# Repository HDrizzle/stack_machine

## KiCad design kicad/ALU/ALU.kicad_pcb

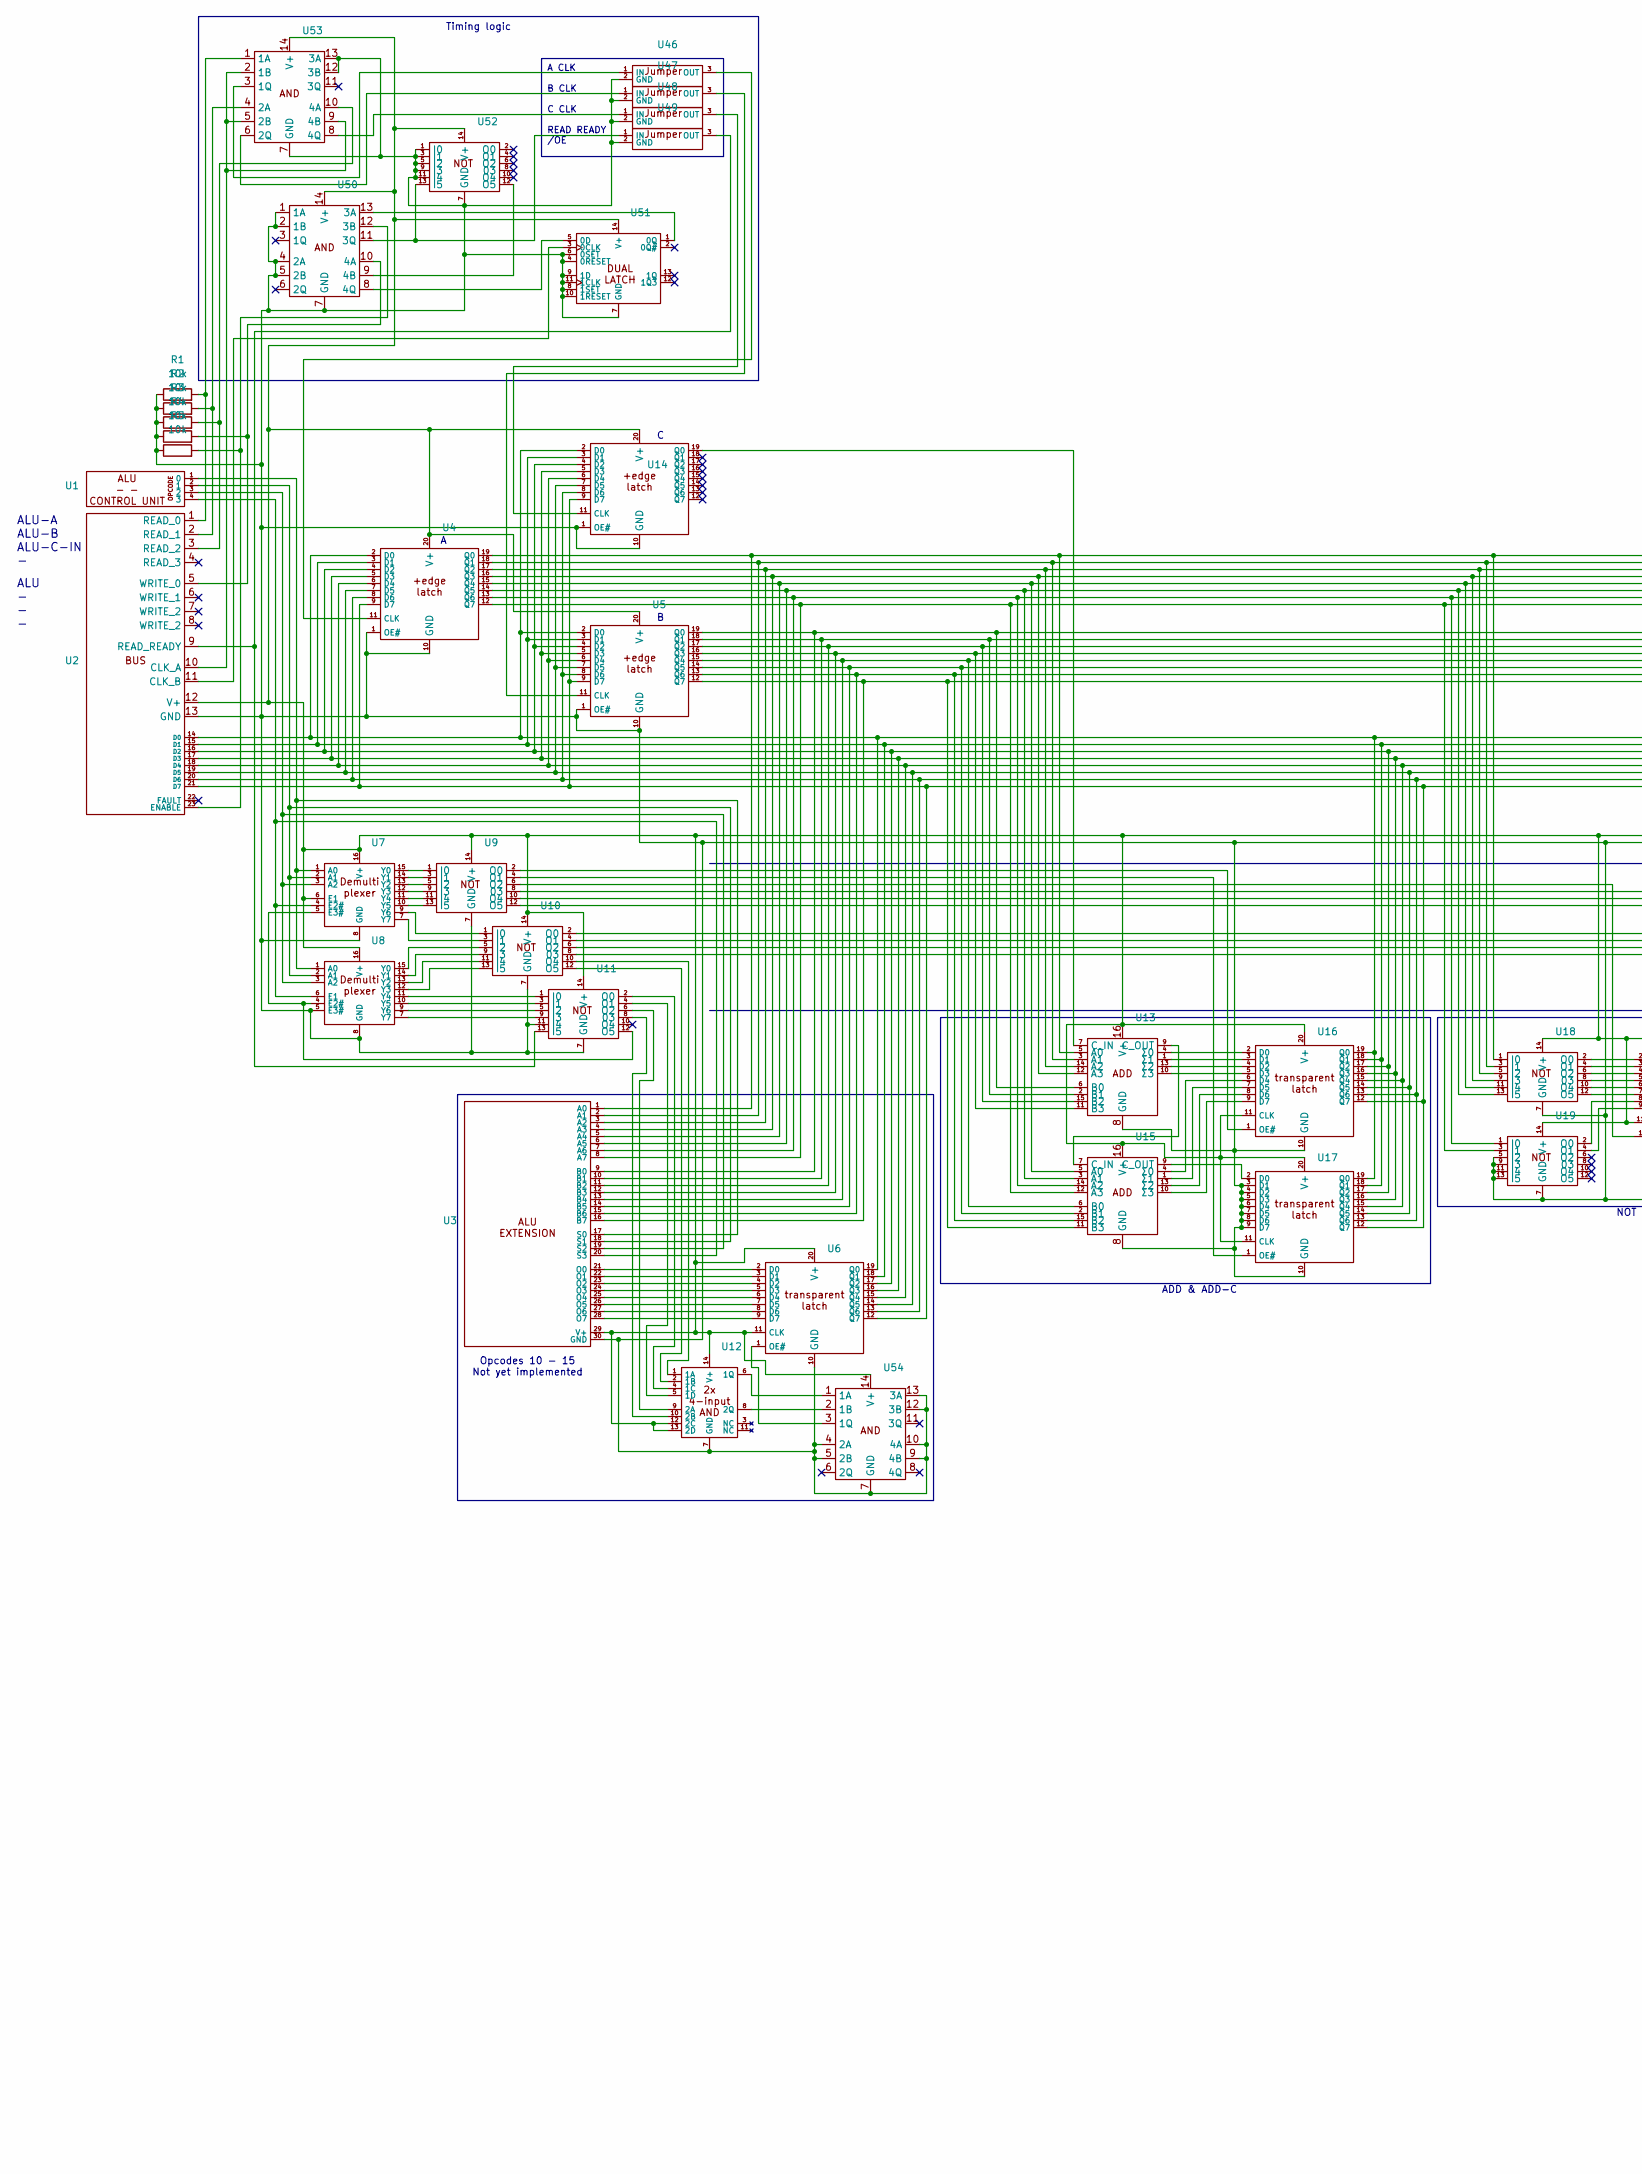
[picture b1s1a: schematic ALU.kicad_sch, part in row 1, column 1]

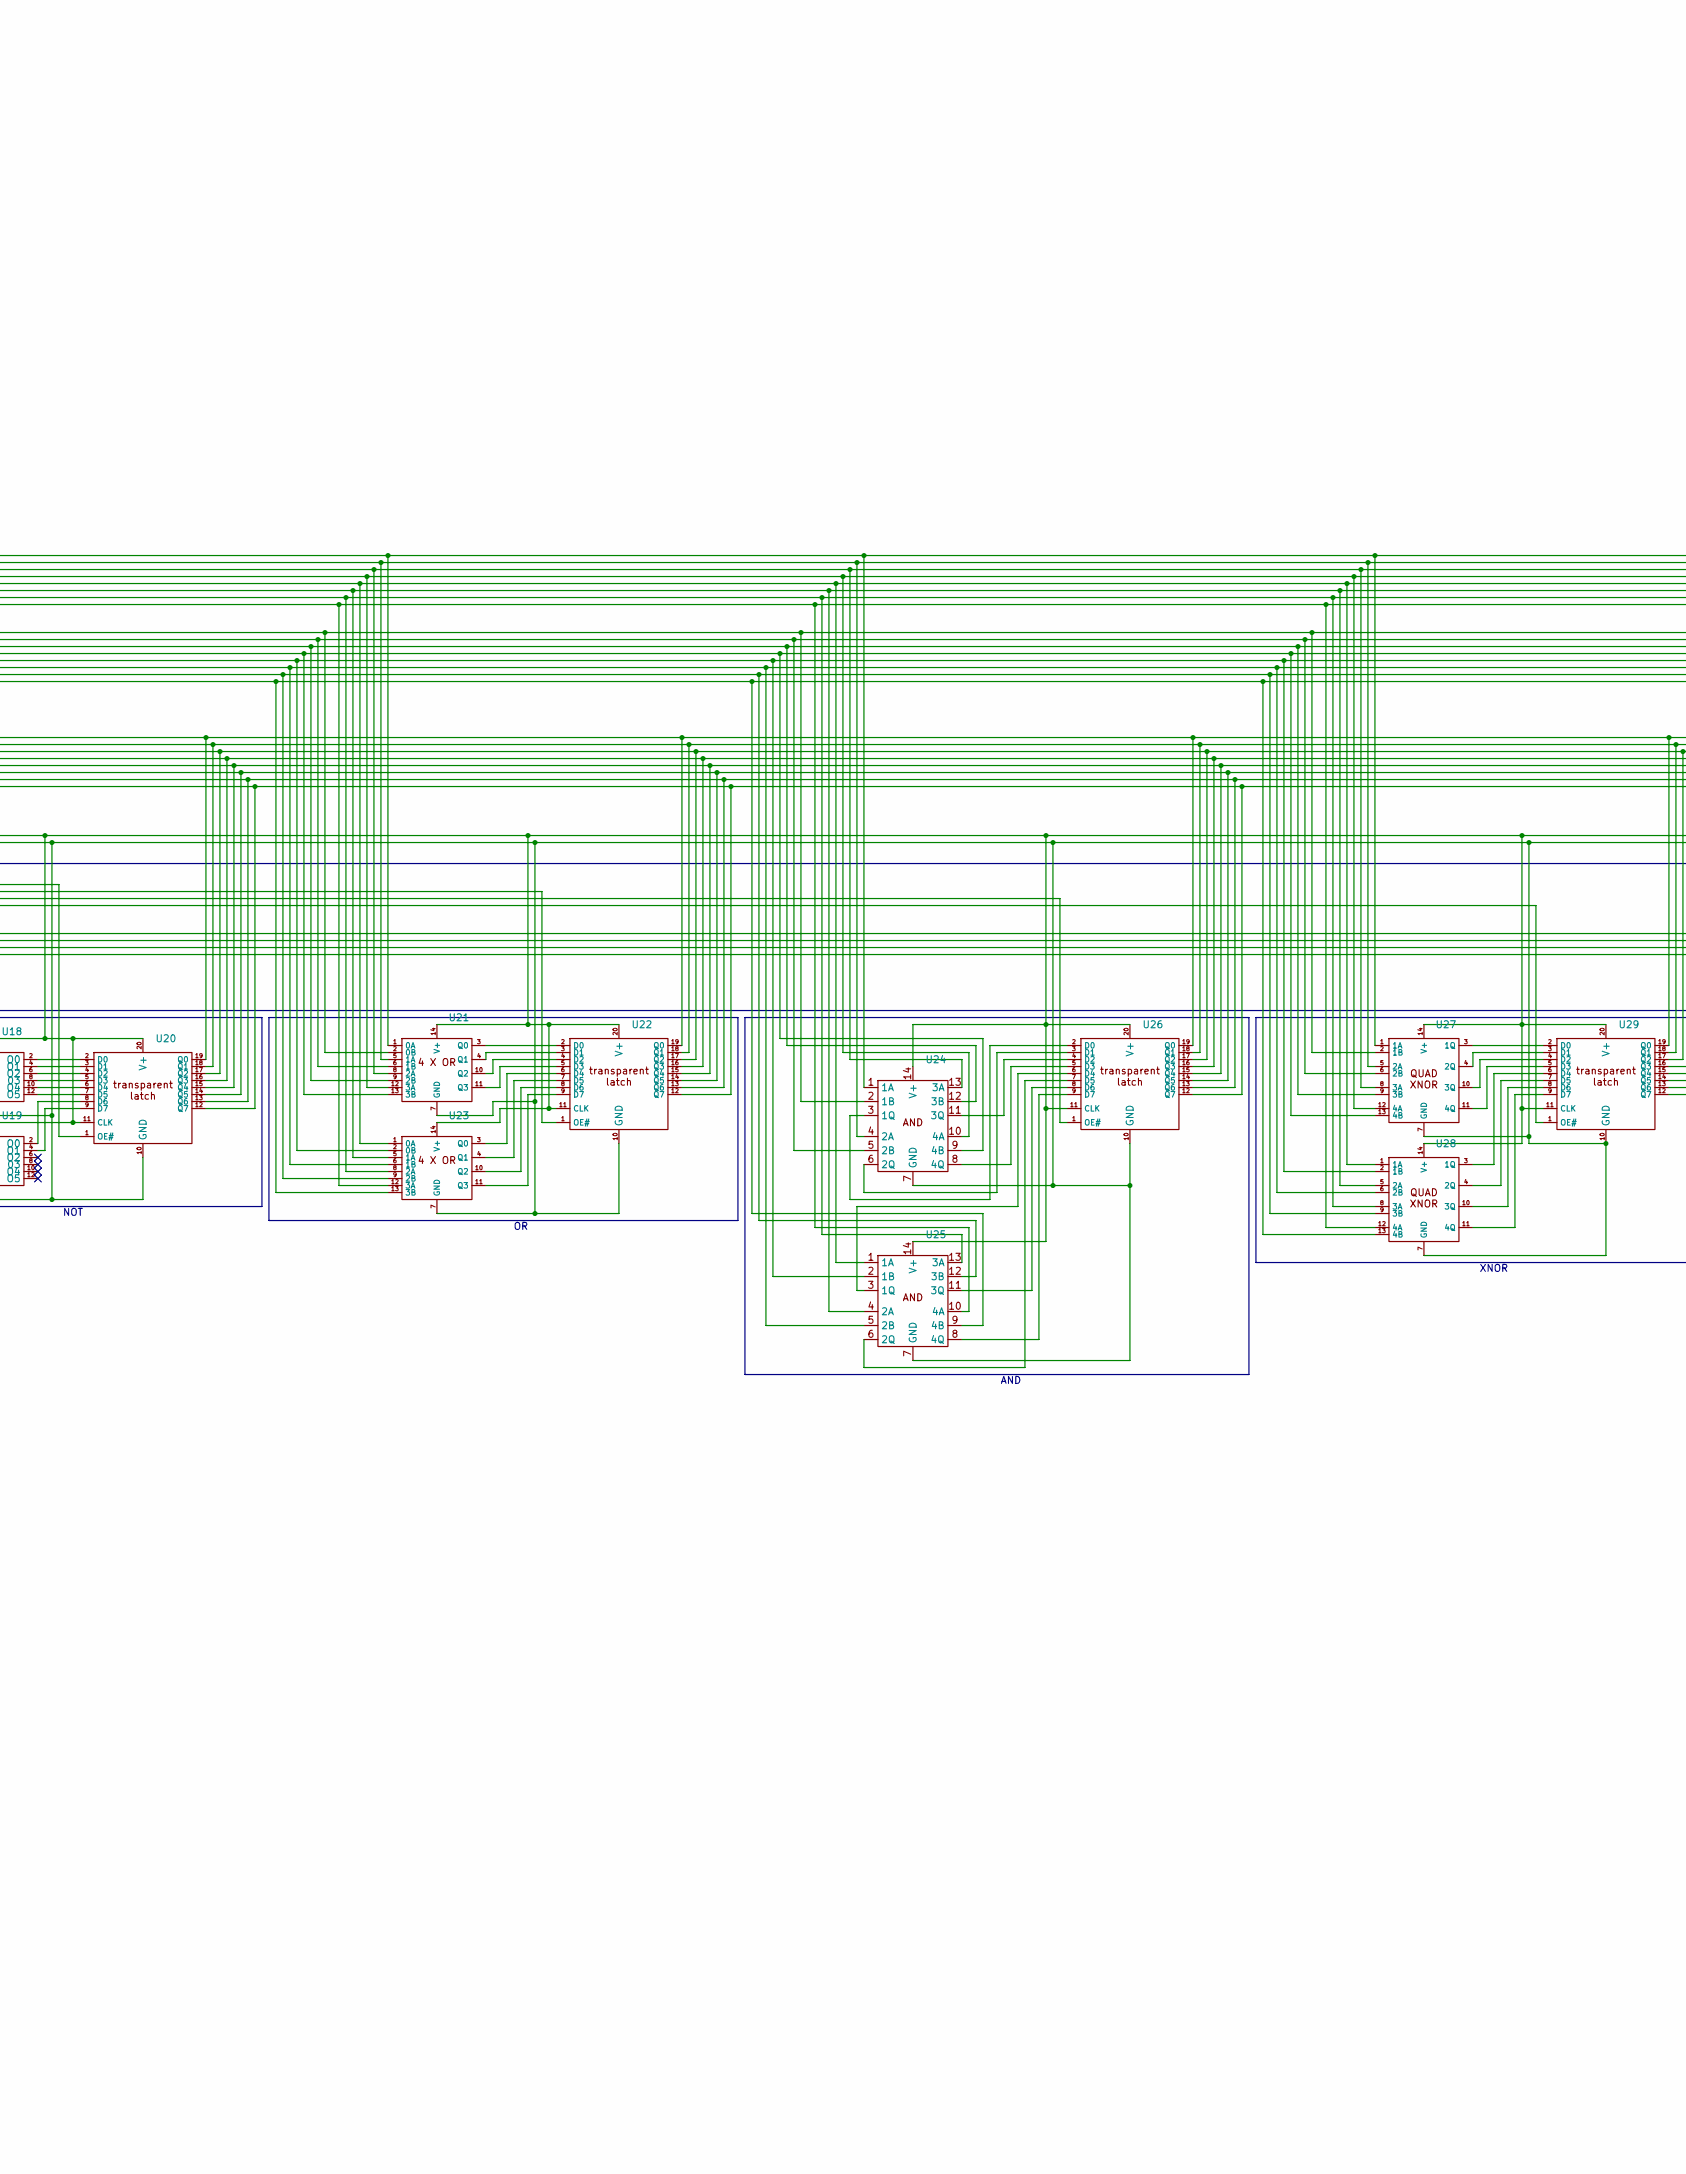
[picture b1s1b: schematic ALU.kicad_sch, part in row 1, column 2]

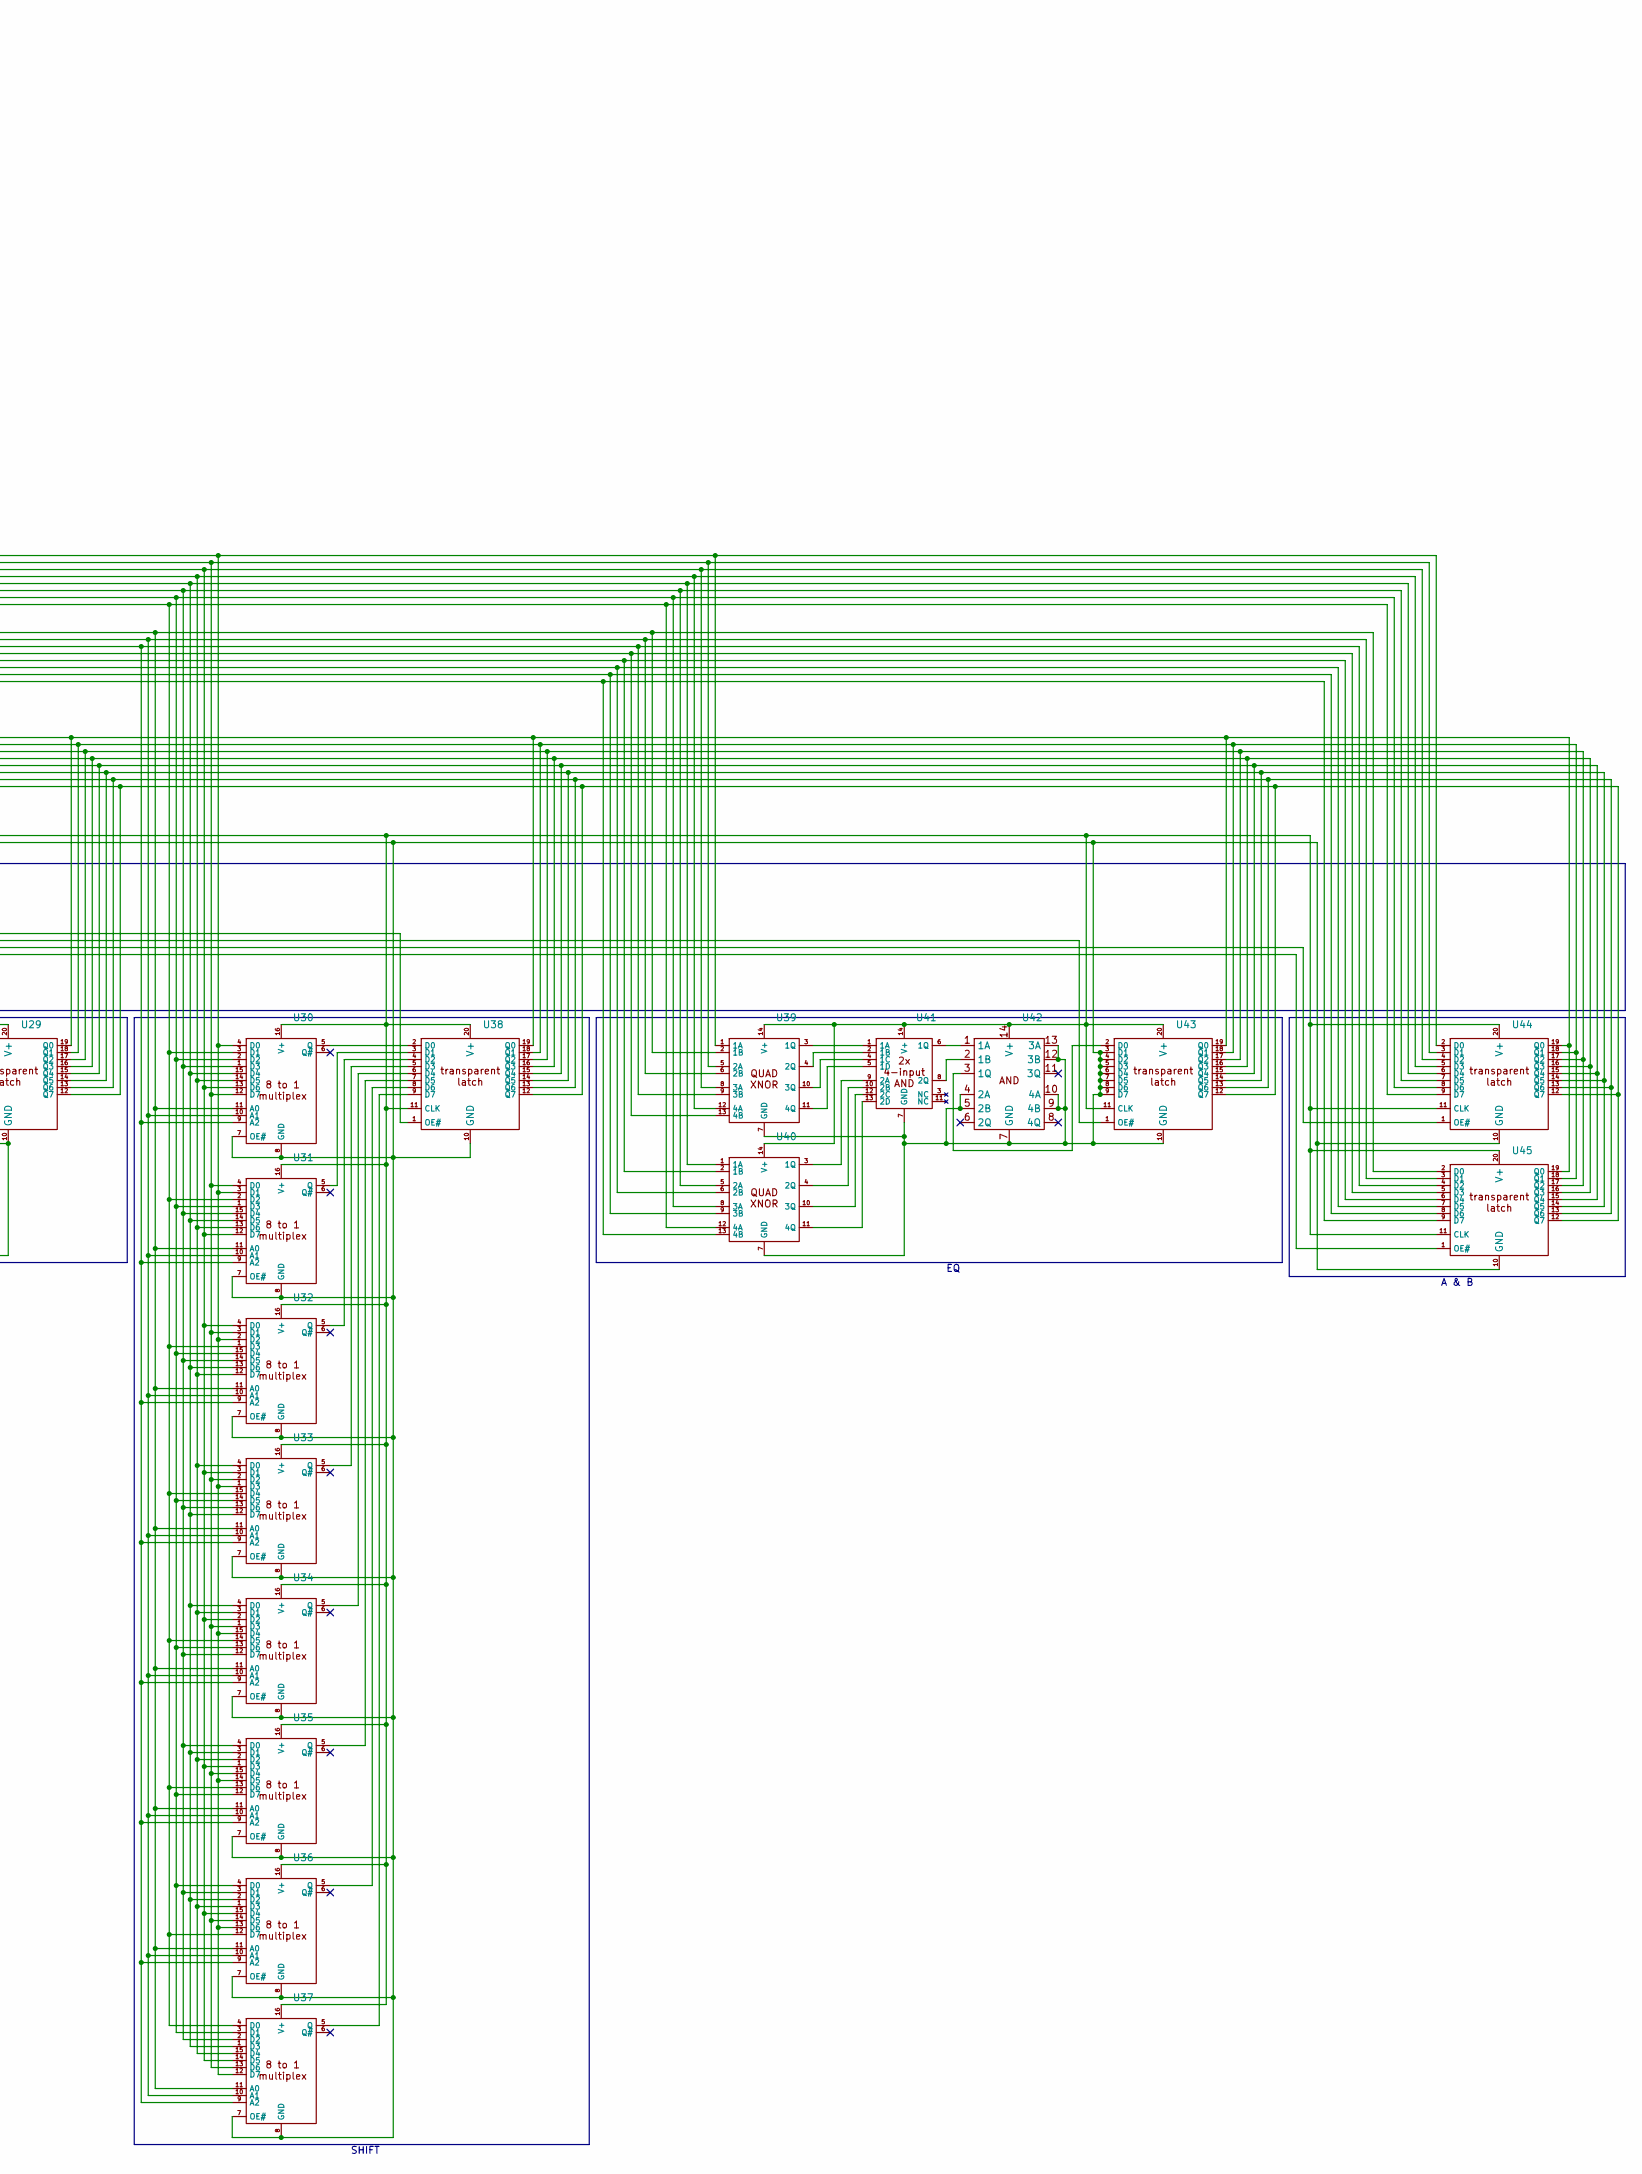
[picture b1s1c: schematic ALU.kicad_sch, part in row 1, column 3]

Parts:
R1, R2, R3, R4, R5: 10k; 0.4_pitch_resistor
U1: PinHeader_1x04_P2.54mm_Vertical
U2: PinHeader_1x23_P2.54mm_Vertical
U3: PinHeader_1x30_P2.54mm_Horizontal
U4, U5, U6, U14, U16, U17, U20, U22, U26, U29, U38, U43, U44, U45: DIP-20_W7.62mm
U7, U8, U13, U15, U30, U31, U32, U33, U34, U35, U36, U37: DIP-16_W7.62mm
U9, U10, U11, U12, U18, U19, U21, U23, U24, U25, U27, U28, U39, U40, U41, U42, U50, U51, U52, U53, U54: DIP-14_W7.62mm
U46, U47, U48, U49: jumper

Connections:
unnamed: U1.1 (0), U3.17 (S0), U7.1 (A0), U8.1 (A0)
unnamed: U1.2 (1), U3.18 (S1), U7.2 (A1), U8.2 (A1)
unnamed: U1.3 (2), U3.19 (S2), U7.3 (A2), U8.3 (A2)
unnamed: U1.4 (3), U3.20 (S3), U7.4 (E2#), U8.6 (E1)
unnamed: U2.10 (CLK_A), U53.2 (1B), U53.5 (2B), U53.9 (4B)
unnamed: U2.11 (CLK_B), U51.3 (0CLK)
unnamed: R5.2, U2.23 (ENABLE), U50.12 (3B)
unnamed: R1.2, U2.1 (READ_0), U53.1 (1A)
unnamed: R2.2, U2.2 (READ_1), U53.4 (2A)
unnamed: R3.2, U2.3 (READ_2), U53.10 (4A)
unnamed: R4.2, U2.5 (WRITE_0), U50.10 (4A)
unnamed: U3.21 (O0), U6.2 (D0)
unnamed: U3.22 (O1), U6.3 (D1)
unnamed: U3.23 (O2), U6.4 (D2)
unnamed: U3.24 (O3), U6.5 (D3)
unnamed: U3.25 (O4), U6.6 (D4)
unnamed: U3.26 (O5), U6.7 (D5)
unnamed: U3.27 (O6), U6.8 (D6)
unnamed: U3.28 (O7), U6.9 (D7)
unnamed: U4.11 (CLK), U46.3 (OUT)
unnamed: U7.15 (Y0), U9.1 (I0)
unnamed: U7.14 (Y1), U9.3 (I1)
unnamed: U7.13 (Y2), U9.5 (I2)
unnamed: U7.12 (Y3), U9.9 (I3)
unnamed: U7.11 (Y4), U9.11 (I4)
unnamed: U7.10 (Y5), U9.13 (I5)
unnamed: U10.8 (03), U45.1 (OE#)
unnamed: R1.1, R2.1, R3.1, R4.1, R5.1, U2.13 (GND), U3.30 (GND), U4.1 (OE#), U4.10 (GND), U5.1 (OE#), U5.10 (GND), U6.10 (GND), U7.8 (GND), U8.5 (E3#), U8.8 (GND), U9.7 (GND), U10.7 (GND), U11.7 (GND), U11.11 (I4), U12.7 (GND), U13.8 (GND), U14.1 (OE#), U14.10 (GND), U15.8 (GND), U16.10 (GND), U17.3 (D1), U17.4 (D2), U17.5 (D3), U17.6 (D4), U17.7 (D5), U17.8 (D6), U17.9 (D7), U17.10 (GND), U18.7 (GND), U19.5 (I2), U19.7 (GND), U19.9 (I3), U19.11 (I4), U19.13 (I5), U20.10 (GND), U21.7 (GND), U22.10 (GND), U23.7 (GND), U24.7 (GND), U25.7 (GND), U26.10 (GND), U27.7 (GND), U28.7 (GND), U29.10 (GND), U30.7 (OE#), U30.8 (GND), U31.7 (OE#), U31.8 (GND), U32.7 (OE#), U32.8 (GND), U33.7 (OE#), U33.8 (GND), U34.7 (OE#), U34.8 (GND), U35.7 (OE#), U35.8 (GND), U36.7 (OE#), U36.8 (GND), U37.7 (OE#), U37.8 (GND), U38.10 (GND), U39.7 (GND), U40.7 (GND), U41.7 (GND), U42.4 (2A), U42.5 (2B), U42.7 (GND), U42.9 (4B), U42.10 (4A), U42.12 (3B), U42.13 (3A), U43.3 (D1), U43.4 (D2), U43.5 (D3), U43.6 (D4), U43.7 (D5), U43.8 (D6), U43.9 (D7), U43.10 (GND), U44.10 (GND), U45.10 (GND), U46.2 (GND), U47.2 (GND), U48.2 (GND), U49.2 (GND), U50.1 (1A), U50.2 (1B), U50.4 (2A), U50.5 (2B), U50.7 (GND), U51.4 (0RESET), U51.6 (0SET), U51.7 (GND), U51.8 (1SET), U51.9 (1D), U51.10 (1RESET), U51.11 (1CLK), U52.1 (I0), U52.3 (I1), U52.5 (I2), U52.7 (GND), U52.9 (I3), U52.11 (I4), U53.7 (GND), U53.12 (3B), U53.13 (3A), U54.4 (2A), U54.5 (2B), U54.7 (GND), U54.9 (4B), U54.10 (4A), U54.12 (3B), U54.13 (3A)
unnamed: U7.9 (Y6), U10.1 (I0)
unnamed: U7.7 (Y7), U10.3 (I1)
unnamed: U8.15 (Y0), U10.5 (I2)
unnamed: U8.14 (Y1), U10.9 (I3)
unnamed: U8.13 (Y2), U10.11 (I4)
unnamed: U8.12 (Y3), U10.13 (I5)
unnamed: U10.2 (O0), U38.1 (OE#)
unnamed: U10.4 (O1), U43.1 (OE#)
unnamed: U10.6 (O2), U44.1 (OE#)
unnamed: U10.10 (O4), U12.1 (1A)
unnamed: U10.12 (O5), U12.2 (1B)
unnamed: U2.12 (V+), U3.29 (V+), U4.20 (V+), U5.20 (V+), U6.11 (CLK), U6.20 (V+), U7.6 (E1), U7.16 (V+), U8.16 (V+), U9.14 (V+), U10.14 (V+), U11.14 (V+), U12.12 (2C), U12.13 (2D), U12.14 (V+), U13.16 (V+), U14.20 (V+), U15.16 (V+), U16.11 (CLK), U16.20 (V+), U17.11 (CLK), U17.20 (V+), U18.14 (V+), U19.14 (V+), U20.11 (CLK), U20.20 (V+), U21.14 (V+), U22.11 (CLK), U22.20 (V+), U23.14 (V+), U24.14 (V+), U25.14 (V+), U26.11 (CLK), U26.20 (V+), U27.14 (V+), U28.14 (V+), U29.11 (CLK), U29.20 (V+), U30.16 (V+), U31.16 (V+), U32.16 (V+), U33.16 (V+), U34.16 (V+), U35.16 (V+), U36.16 (V+), U37.16 (V+), U38.11 (CLK), U38.20 (V+), U39.14 (V+), U40.14 (V+), U41.14 (V+), U42.14 (V+), U43.11 (CLK), U43.20 (V+), U44.11 (CLK), U44.20 (V+), U45.11 (CLK), U45.20 (V+), U50.14 (V+), U51.14 (V+), U52.14 (V+), U53.14 (V+), U54.14 (V+)
unnamed: U11.8 (03), U12.10 (2B)
unnamed: U8.11 (Y4), U11.1 (I0)
unnamed: U8.10 (Y5), U11.3 (I1)
unnamed: U8.9 (Y6), U11.5 (I2)
unnamed: U8.7 (Y7), U11.9 (I3)
unnamed: U2.9 (READ_READY), U11.13 (I5), U49.3 (OUT)
unnamed: U11.2 (O0), U12.4 (1C)
unnamed: U11.4 (O1), U12.5 (1D)
unnamed: U11.6 (O2), U12.9 (2A)
unnamed: U7.5 (E3#), U8.4 (E2#), U11.12 (O5)
unnamed: U12.6 (1Q), U54.1 (1A)
unnamed: U12.8 (2Q), U54.2 (1B)
unnamed: U3.1 (A0), U4.19 (Q0), U13.5 (A0), U18.1 (I0), U21.1 (0A), U24.1 (1A), U27.1 (1A), U30.4 (D0), U31.3 (D1), U32.2 (D2), U33.1 (D3), U34.15 (D4), U35.14 (D5), U36.13 (D6), U37.12 (D7), U39.1 (1A), U44.2 (D0)
unnamed: U3.2 (A1), U4.18 (Q1), U13.3 (A1), U18.3 (I1), U21.5 (1A), U24.4 (2A), U27.5 (2A), U30.12 (D7), U31.4 (D0), U32.3 (D1), U33.2 (D2), U34.1 (D3), U35.15 (D4), U36.14 (D5), U37.13 (D6), U39.5 (2A), U44.3 (D1)
unnamed: U3.3 (A2), U4.17 (Q2), U13.14 (A2), U18.5 (I2), U21.8 (2A), U24.13 (3A), U27.8 (3A), U30.13 (D6), U31.12 (D7), U32.4 (D0), U33.3 (D1), U34.2 (D2), U35.1 (D3), U36.15 (D4), U37.14 (D5), U39.8 (3A), U44.4 (D2)
unnamed: U3.4 (A3), U4.16 (Q3), U13.12 (A3), U18.9 (I3), U21.12 (3A), U24.10 (4A), U27.12 (4A), U30.14 (D5), U31.13 (D6), U32.12 (D7), U33.4 (D0), U34.3 (D1), U35.2 (D2), U36.1 (D3), U37.15 (D4), U39.12 (4A), U44.5 (D3)
unnamed: U3.9 (B0), U5.19 (Q0), U13.6 (B0), U21.2 (0B), U24.2 (1B), U27.2 (1B), U30.11 (A0), U31.11 (A0), U32.11 (A0), U33.11 (A0), U34.11 (A0), U35.11 (A0), U36.11 (A0), U37.11 (A0), U39.2 (1B), U45.2 (D0)
unnamed: U3.10 (B1), U5.18 (Q1), U13.2 (B1), U21.6 (1B), U24.5 (2B), U27.6 (2B), U30.10 (A1), U31.10 (A1), U32.10 (A1), U33.10 (A1), U34.10 (A1), U35.10 (A1), U36.10 (A1), U37.10 (A1), U39.6 (2B), U45.3 (D1)
unnamed: U3.11 (B2), U5.17 (Q2), U13.15 (B2), U21.9 (2B), U24.12 (3B), U27.9 (3B), U30.9 (A2), U31.9 (A2), U32.9 (A2), U33.9 (A2), U34.9 (A2), U35.9 (A2), U36.9 (A2), U37.9 (A2), U39.9 (3B), U45.4 (D2)
unnamed: U3.12 (B3), U5.16 (Q3), U13.11 (B3), U21.13 (3B), U24.9 (4B), U27.13 (4B), U39.13 (4B), U45.5 (D3)
unnamed: U13.7 (C_IN), U14.19 (Q0)
unnamed: U13.9 (C_OUT), U15.7 (C_IN)
unnamed: U13.4 (Σ0), U16.2 (D0)
unnamed: U13.1 (Σ1), U16.3 (D1)
unnamed: U13.13 (Σ2), U16.4 (D2)
unnamed: U13.10 (Σ3), U16.5 (D3)
unnamed: U14.11 (CLK), U48.3 (OUT)
unnamed: U2.14 (D0), U4.2 (D0), U5.2 (D0), U6.19 (Q0), U14.2 (D0), U16.19 (Q0), U17.19 (Q0), U20.19 (Q0), U22.19 (Q0), U26.19 (Q0), U29.19 (Q0), U38.19 (Q0), U43.19 (Q0), U44.19 (Q0), U45.19 (Q0)
unnamed: U2.15 (D1), U4.3 (D1), U5.3 (D1), U6.18 (Q1), U14.3 (D1), U16.18 (Q1), U17.18 (Q1), U20.18 (Q1), U22.18 (Q1), U26.18 (Q1), U29.18 (Q1), U38.18 (Q1), U43.18 (Q1), U44.18 (Q1), U45.18 (Q1)
unnamed: U2.16 (D2), U4.4 (D2), U5.4 (D2), U6.17 (Q2), U14.4 (D2), U16.17 (Q2), U17.17 (Q2), U20.17 (Q2), U22.17 (Q2), U26.17 (Q2), U29.17 (Q2), U38.17 (Q2), U43.17 (Q2), U44.17 (Q2), U45.17 (Q2)
unnamed: U2.17 (D3), U4.5 (D3), U5.5 (D3), U6.16 (Q3), U14.5 (D3), U16.16 (Q3), U17.16 (Q3), U20.16 (Q3), U22.16 (Q3), U26.16 (Q3), U29.16 (Q3), U38.16 (Q3), U43.16 (Q3), U44.16 (Q3), U45.16 (Q3)
unnamed: U2.18 (D4), U4.6 (D4), U5.6 (D4), U6.15 (Q4), U14.6 (D4), U16.15 (Q4), U17.15 (Q4), U20.15 (Q4), U22.15 (Q4), U26.15 (Q4), U29.15 (Q4), U38.15 (Q4), U43.15 (Q4), U44.15 (Q4), U45.15 (Q4)
unnamed: U2.19 (D5), U4.7 (D5), U5.7 (D5), U6.14 (Q5), U14.7 (D5), U16.14 (Q5), U17.14 (Q5), U20.14 (Q5), U22.14 (Q5), U26.14 (Q5), U29.14 (Q5), U38.14 (Q5), U43.14 (Q5), U44.14 (Q5), U45.14 (Q5)
unnamed: U2.20 (D6), U4.8 (D6), U5.8 (D6), U6.13 (Q6), U14.8 (D6), U16.13 (Q6), U17.13 (Q6), U20.13 (Q6), U22.13 (Q6), U26.13 (Q6), U29.13 (Q6), U38.13 (Q6), U43.13 (Q6), U44.13 (Q6), U45.13 (Q6)
unnamed: U2.21 (D7), U4.9 (D7), U5.9 (D7), U6.12 (Q7), U14.9 (D7), U16.12 (Q7), U17.12 (Q7), U20.12 (Q7), U22.12 (Q7), U26.12 (Q7), U29.12 (Q7), U38.12 (Q7), U43.12 (Q7), U44.12 (Q7), U45.12 (Q7)
unnamed: U3.5 (A4), U4.15 (Q4), U15.5 (A0), U18.11 (I4), U23.1 (0A), U25.1 (1A), U28.1 (1A), U30.15 (D4), U31.14 (D5), U32.13 (D6), U33.12 (D7), U34.4 (D0), U35.3 (D1), U36.2 (D2), U37.1 (D3), U40.1 (1A), U44.6 (D4)
unnamed: U3.6 (A5), U4.14 (Q5), U15.3 (A1), U18.13 (I5), U23.5 (1A), U25.4 (2A), U28.5 (2A), U30.1 (D3), U31.15 (D4), U32.14 (D5), U33.13 (D6), U34.12 (D7), U35.4 (D0), U36.3 (D1), U37.2 (D2), U40.5 (2A), U44.7 (D5)
unnamed: U3.7 (A6), U4.13 (Q6), U15.14 (A2), U19.1 (I0), U23.8 (2A), U25.13 (3A), U28.8 (3A), U30.2 (D2), U31.1 (D3), U32.15 (D4), U33.14 (D5), U34.13 (D6), U35.12 (D7), U36.4 (D0), U37.3 (D1), U40.8 (3A), U44.8 (D6)
unnamed: U3.8 (A7), U4.12 (Q7), U15.12 (A3), U19.3 (I1), U23.12 (3A), U25.10 (4A), U28.12 (4A), U30.3 (D1), U31.2 (D2), U32.1 (D3), U33.15 (D4), U34.14 (D5), U35.13 (D6), U36.12 (D7), U37.4 (D0), U40.12 (4A), U44.9 (D7)
unnamed: U3.13 (B4), U5.15 (Q4), U15.6 (B0), U23.2 (0B), U25.2 (1B), U28.2 (1B), U40.2 (1B), U45.6 (D4)
unnamed: U3.14 (B5), U5.14 (Q5), U15.2 (B1), U23.6 (1B), U25.5 (2B), U28.6 (2B), U40.6 (2B), U45.7 (D5)
unnamed: U3.15 (B6), U5.13 (Q6), U15.15 (B2), U23.9 (2B), U25.12 (3B), U28.9 (3B), U40.9 (3B), U45.8 (D6)
unnamed: U3.16 (B7), U5.12 (Q7), U15.11 (B3), U23.13 (3B), U25.9 (4B), U28.13 (4B), U40.13 (4B), U45.9 (D7)
unnamed: U15.9 (C_OUT), U17.2 (D0)
unnamed: U15.4 (Σ0), U16.6 (D4)
unnamed: U15.1 (Σ1), U16.7 (D5)
unnamed: U15.13 (Σ2), U16.8 (D6)
unnamed: U15.10 (Σ3), U16.9 (D7)
unnamed: U9.2 (O0), U16.1 (OE#)
unnamed: U9.4 (O1), U17.1 (OE#)
unnamed: U18.8 (03), U20.5 (D3)
unnamed: U18.2 (O0), U20.2 (D0)
unnamed: U18.4 (O1), U20.3 (D1)
unnamed: U18.6 (O2), U20.4 (D2)
unnamed: U18.10 (O4), U20.6 (D4)
unnamed: U18.12 (O5), U20.7 (D5)
unnamed: U19.2 (O0), U20.8 (D6)
unnamed: U19.4 (O1), U20.9 (D7)
unnamed: U9.6 (O2), U20.1 (OE#)
unnamed: U21.3 (Q0), U22.2 (D0)
unnamed: U21.4 (Q1), U22.3 (D1)
unnamed: U21.10 (Q2), U22.4 (D2)
unnamed: U21.11 (Q3), U22.5 (D3)
unnamed: U22.6 (D4), U23.3 (Q0)
unnamed: U22.7 (D5), U23.4 (Q1)
unnamed: U22.8 (D6), U23.10 (Q2)
unnamed: U22.9 (D7), U23.11 (Q3)
unnamed: U9.8 (03), U22.1 (OE#)
unnamed: U24.3 (1Q), U26.2 (D0)
unnamed: U24.6 (2Q), U26.3 (D1)
unnamed: U24.11 (3Q), U26.4 (D2)
unnamed: U24.8 (4Q), U26.5 (D3)
unnamed: U25.3 (1Q), U26.6 (D4)
unnamed: U25.6 (2Q), U26.7 (D5)
unnamed: U25.11 (3Q), U26.8 (D6)
unnamed: U25.8 (4Q), U26.9 (D7)
unnamed: U9.10 (O4), U26.1 (OE#)
unnamed: U27.3 (1Q), U29.2 (D0)
unnamed: U27.4 (2Q), U29.3 (D1)
unnamed: U27.10 (3Q), U29.4 (D2)
unnamed: U27.11 (4Q), U29.5 (D3)
unnamed: U28.3 (1Q), U29.6 (D4)
unnamed: U28.4 (2Q), U29.7 (D5)
unnamed: U28.10 (3Q), U29.8 (D6)
unnamed: U28.11 (4Q), U29.9 (D7)
unnamed: U9.12 (O5), U29.1 (OE#)
unnamed: U30.5 (Q), U38.2 (D0)
unnamed: U31.5 (Q), U38.3 (D1)
unnamed: U32.5 (Q), U38.4 (D2)
unnamed: U33.5 (Q), U38.5 (D3)
unnamed: U34.5 (Q), U38.6 (D4)
unnamed: U35.5 (Q), U38.7 (D5)
unnamed: U36.5 (Q), U38.8 (D6)
unnamed: U37.5 (Q), U38.9 (D7)
unnamed: U39.3 (1Q), U41.1 (1A)
unnamed: U39.4 (2Q), U41.2 (1B)
unnamed: U39.10 (3Q), U41.4 (1C)
unnamed: U39.11 (4Q), U41.5 (1D)
unnamed: U40.3 (1Q), U41.9 (2A)
unnamed: U40.4 (2Q), U41.10 (2B)
unnamed: U40.10 (3Q), U41.12 (2C)
unnamed: U40.11 (4Q), U41.13 (2D)
unnamed: U41.6 (1Q), U42.1 (1A)
unnamed: U41.8 (2Q), U42.2 (1B)
unnamed: U42.3 (1Q), U43.2 (D0)
unnamed: U46.1 (IN), U53.3 (1Q)
unnamed: U47.1 (IN), U53.6 (2Q)
unnamed: U5.11 (CLK), U47.3 (OUT)
unnamed: U48.1 (IN), U53.8 (4Q)
unnamed: U49.1 (IN), U50.11 (3Q), U52.13 (I5)
unnamed: U50.13 (3A), U51.1 (0Q)
unnamed: U50.9 (4B), U52.12 (O5)
unnamed: U50.8 (4Q), U51.5 (0D)
unnamed: U6.1 (OE#), U54.3 (1Q)

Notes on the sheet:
Timing logic
A CLK B CLK C CLK READ READY /OE
ALU - - -
ALU-A ALU-B ALU-C-IN -
A & B
SHIFT
AND
NOT
ADD & ADD-C
XNOR
Opcodes 10 - 15 Not yet implemented

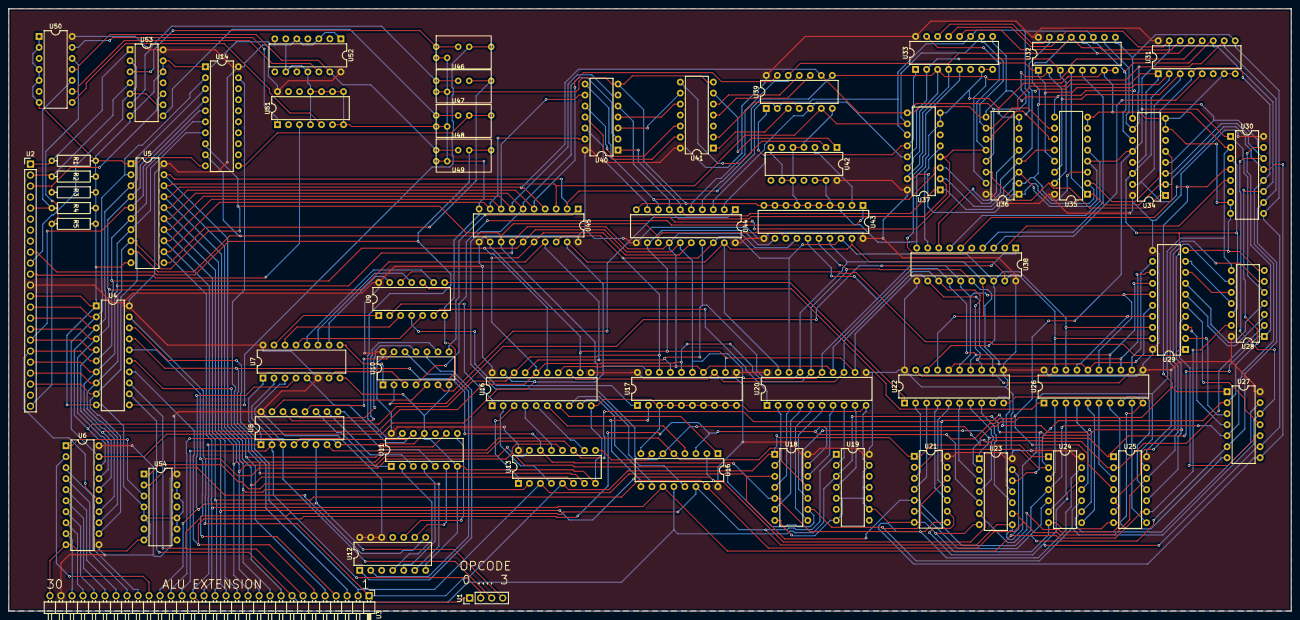
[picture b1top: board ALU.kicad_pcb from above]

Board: 2 copper layers, 296.0 x 139.0 mm, 59 parts (0 on the bottom side), 154 nets.

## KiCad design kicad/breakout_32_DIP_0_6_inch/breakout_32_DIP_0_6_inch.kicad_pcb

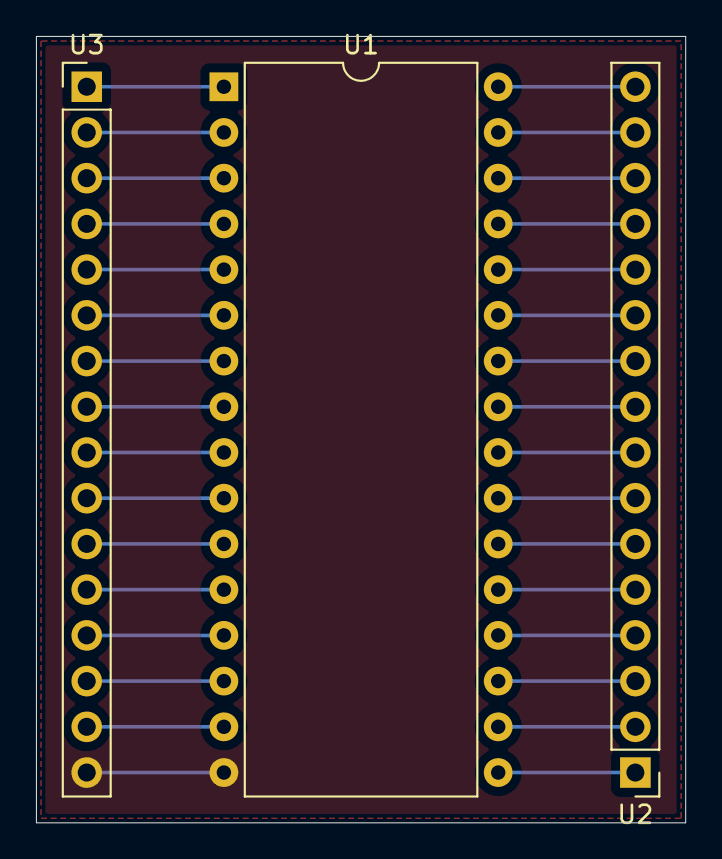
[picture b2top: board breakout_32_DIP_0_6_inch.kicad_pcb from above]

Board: 2 copper layers, 36.1 x 43.7 mm, 3 parts (0 on the bottom side), 30 nets.

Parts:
U1: DIP-32_W15.24mm
U2, U3: PinHeader_1x16_P2.54mm_Vertical

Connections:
unnamed: U1.12 (A0), U3.12 (11)
unnamed: U1.11 (A1), U3.11 (10)
unnamed: U1.10 (A2), U3.10 (9)
unnamed: U1.9 (A3), U3.9 (8)
unnamed: U1.8 (A4), U3.8 (7)
unnamed: U1.7 (A5), U3.7 (6)
unnamed: U1.6 (A6), U3.6 (5)
unnamed: U1.5 (A7), U3.5 (4)
unnamed: U1.27 (A8), U2.11 (10)
unnamed: U1.26 (A9), U2.10 (9)
unnamed: U1.23 (A10), U2.7 (6)
unnamed: U1.25 (A11), U2.9 (8)
unnamed: U1.4 (A12), U3.4 (3)
unnamed: U1.28 (A13), U2.12 (11)
unnamed: U1.29 (A14), U2.13 (12)
unnamed: U1.3 (A15), U3.3 (2)
unnamed: U1.2 (A16), U3.2 (1)
unnamed: U1.22 (CE#), U2.6 (5)
unnamed: U1.13 (DQ0), U3.13 (12)
unnamed: U1.14 (DQ1), U3.14 (13)
unnamed: U1.15 (DQ2), U3.15 (14)
unnamed: U1.17 (DQ3), U2.1 (0)
unnamed: U1.18 (DQ4), U2.2 (1)
unnamed: U1.19 (DQ5), U2.3 (2)
unnamed: U1.20 (DQ6), U2.4 (3)
unnamed: U1.21 (DQ7), U2.5 (4)
unnamed: U1.16 (GND), U3.16 (15)
unnamed: U1.24 (OE#), U2.8 (7)
unnamed: U1.32 (V+), U2.16 (15)
unnamed: U1.31 (WE#), U2.15 (14)
